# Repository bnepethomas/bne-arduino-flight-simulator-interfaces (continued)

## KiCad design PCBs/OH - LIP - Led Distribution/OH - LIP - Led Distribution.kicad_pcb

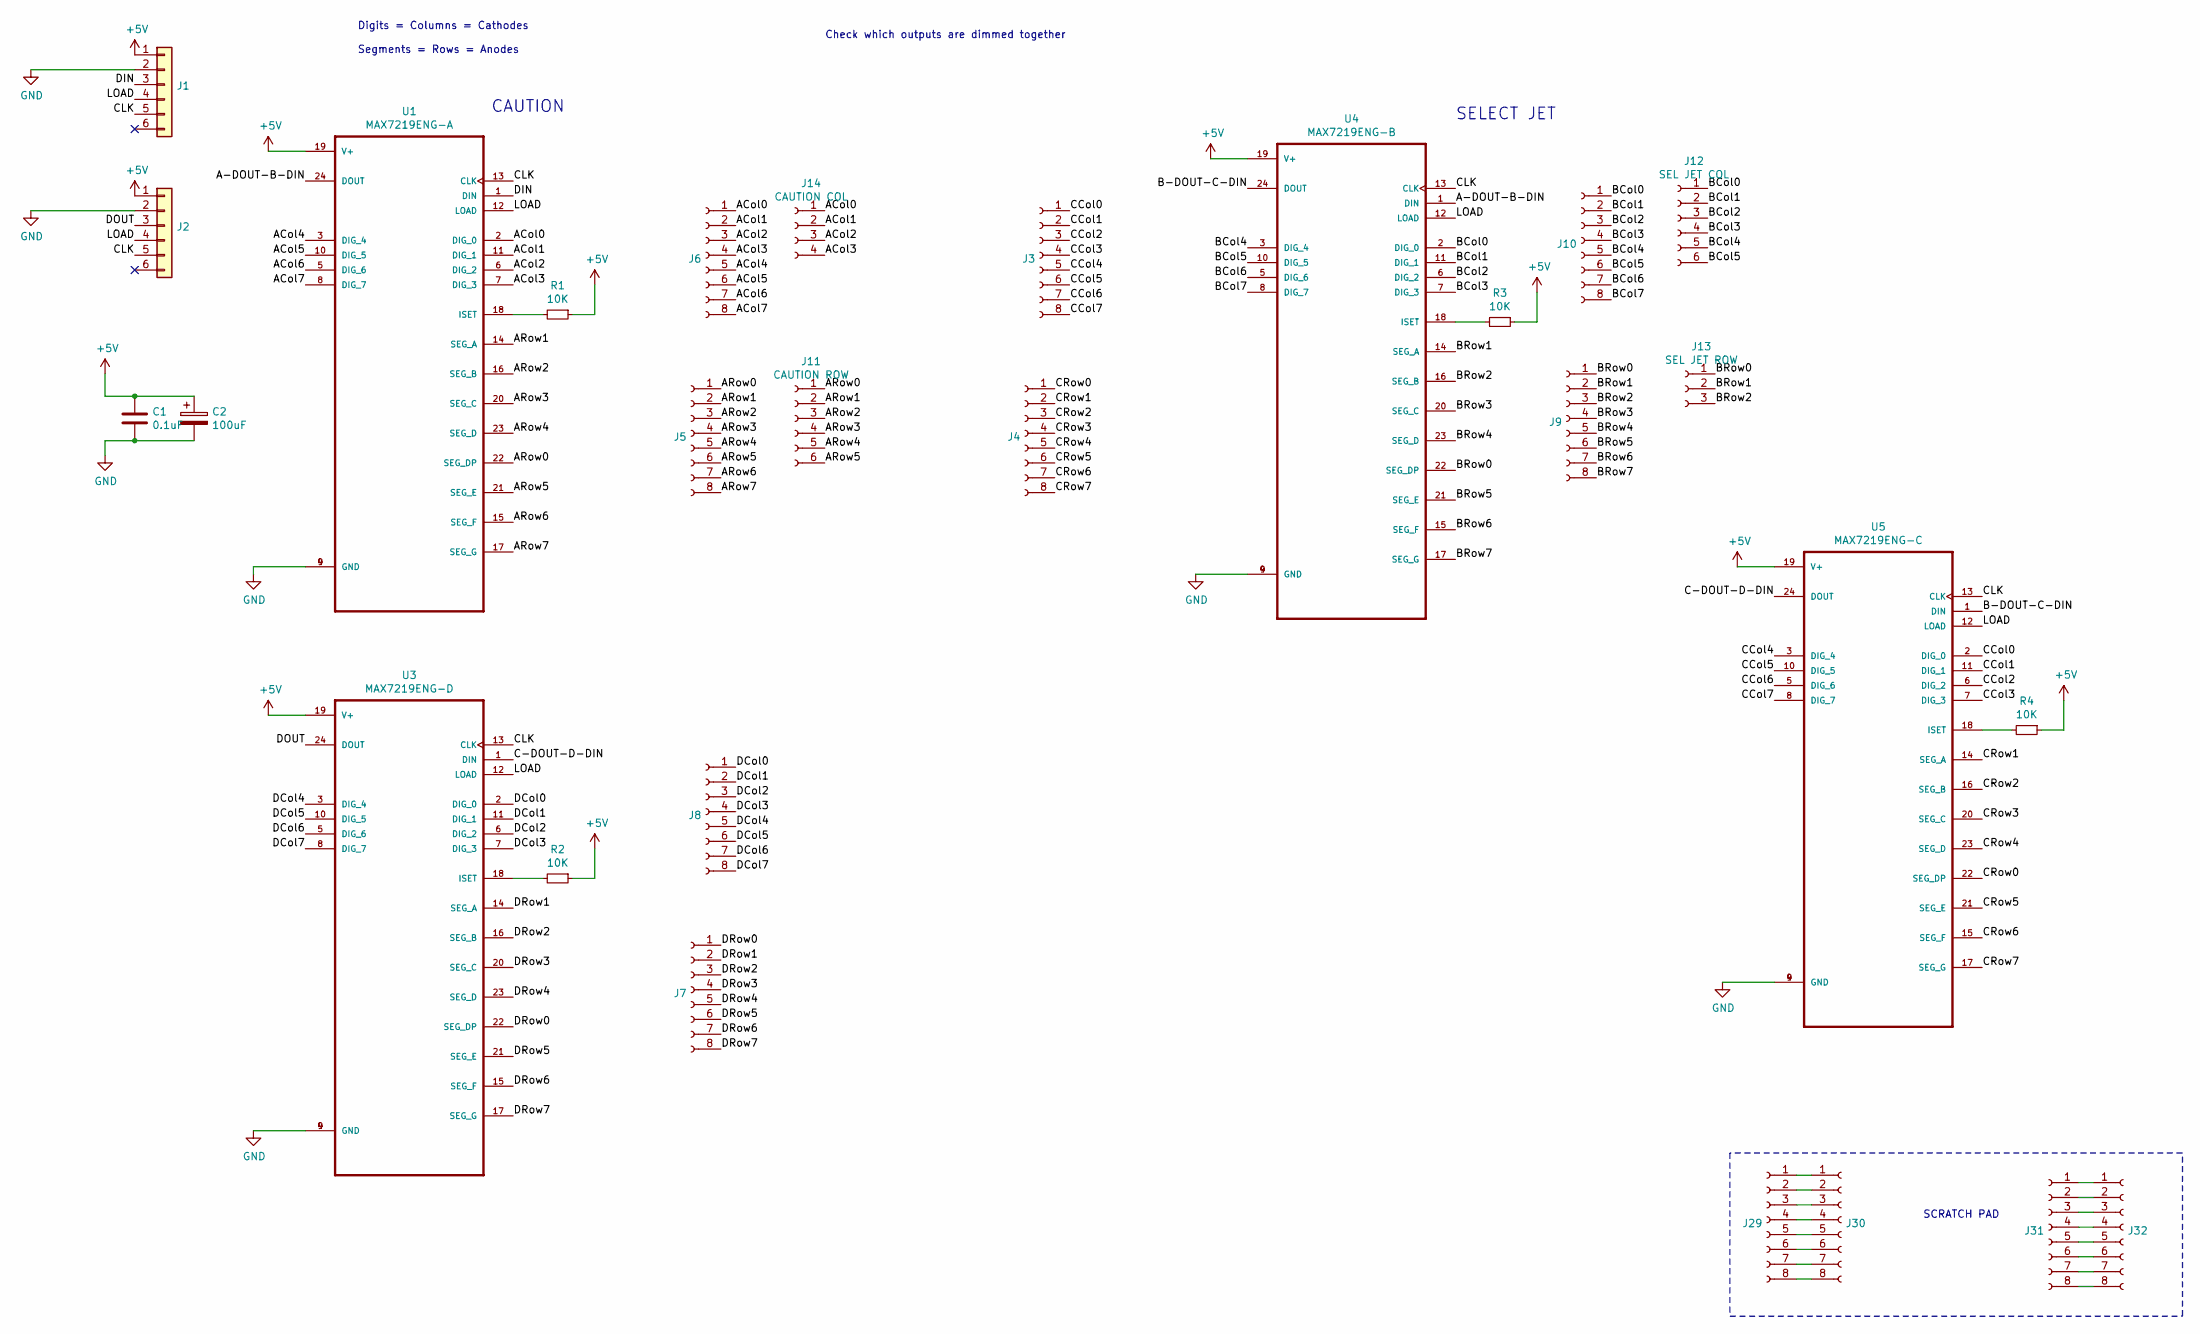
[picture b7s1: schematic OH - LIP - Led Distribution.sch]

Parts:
C1: 0.1uF; C_Disc_D5.1mm_W3.2mm_P5.00mm
C2: 100uF; CP_Radial_D8.0mm_P5.00mm
J1, J2: PinHeader_1x06_P2.54mm_Vertical
J3, J4, J5, J6, J7, J8, J9, J10, J29, J30, J31, J32: PinHeader_1x08_P2.54mm_Vertical
J11: CAUTION ROW; Molex_1x08_P2.54mm_Vertical
J12: SEL JET COL; Molex_1x06_P2.54mm_Vertical
J13: SEL JET ROW; Molex_1x03_P2.54mm_Vertical
J14: CAUTION COL; Molex_1x04_P2.54mm_Vertical
R1, R2, R3, R4: 10K; R_Axial_DIN0309_L9.0mm_D3.2mm_P5.08mm_Vertical
U1: MAX7219ENG-A; DIP-24_W7.62mm_Socket
U3: MAX7219ENG-D; DIP-24_W7.62mm_Socket
U4: MAX7219ENG-B; DIP-24_W7.62mm_Socket
U5: MAX7219ENG-C; DIP-24_W7.62mm_Socket

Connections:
+5V: C1.1, C2.1, J1.1, J2.1, R1.1, R2.1, R3.1, R4.1, U1.19 (V+), U3.19 (V+), U4.19 (V+), U5.19 (V+)
/A-DOUT-B-DIN: U1.24 (DOUT), U4.1 (DIN)
/ACol0: J6.1, J14.1, U1.2 (DIG_0)
/ACol1: J6.2, J14.2, U1.11 (DIG_1)
/ACol2: J6.3, J14.3, U1.6 (DIG_2)
/ACol3: J6.4, J14.4, U1.7 (DIG_3)
/ACol4: J6.5, U1.3 (DIG_4)
/ACol5: J6.6, U1.10 (DIG_5)
/ACol6: J6.7, U1.5 (DIG_6)
/ACol7: J6.8, U1.8 (DIG_7)
/ARow0: J5.1, J11.1, U1.22 (SEG_DP)
/ARow1: J5.2, J11.2, U1.14 (SEG_A)
/ARow2: J5.3, J11.3, U1.16 (SEG_B)
/ARow3: J5.4, J11.4, U1.20 (SEG_C)
/ARow4: J5.5, J11.5, U1.23 (SEG_D)
/ARow5: J5.6, J11.6, U1.21 (SEG_E)
/ARow6: J5.7, U1.15 (SEG_F)
/ARow7: J5.8, U1.17 (SEG_G)
/B-DOUT-C-DIN: U4.24 (DOUT), U5.1 (DIN)
/BCol0: J10.1, J12.1, U4.2 (DIG_0)
/BCol1: J10.2, J12.2, U4.11 (DIG_1)
/BCol2: J10.3, J12.3, U4.6 (DIG_2)
/BCol3: J10.4, J12.4, U4.7 (DIG_3)
/BCol4: J10.5, J12.5, U4.3 (DIG_4)
/BCol5: J10.6, J12.6, U4.10 (DIG_5)
/BCol6: J10.7, U4.5 (DIG_6)
/BCol7: J10.8, U4.8 (DIG_7)
/BRow0: J9.1, J13.1, U4.22 (SEG_DP)
/BRow1: J9.2, J13.2, U4.14 (SEG_A)
/BRow2: J9.3, J13.3, U4.16 (SEG_B)
/BRow3: J9.4, U4.20 (SEG_C)
/BRow4: J9.5, U4.23 (SEG_D)
/BRow5: J9.6, U4.21 (SEG_E)
/BRow6: J9.7, U4.15 (SEG_F)
/BRow7: J9.8, U4.17 (SEG_G)
/C-DOUT-D-DIN: U3.1 (DIN), U5.24 (DOUT)
/CCol0: J3.1, U5.2 (DIG_0)
/CCol1: J3.2, U5.11 (DIG_1)
/CCol2: J3.3, U5.6 (DIG_2)
/CCol3: J3.4, U5.7 (DIG_3)
/CCol4: J3.5, U5.3 (DIG_4)
/CCol5: J3.6, U5.10 (DIG_5)
/CCol6: J3.7, U5.5 (DIG_6)
/CCol7: J3.8, U5.8 (DIG_7)
/CLK: J1.5, J2.5, U1.13 (CLK), U3.13 (CLK), U4.13 (CLK), U5.13 (CLK)
/CRow0: J4.1, U5.22 (SEG_DP)
/CRow1: J4.2, U5.14 (SEG_A)
/CRow2: J4.3, U5.16 (SEG_B)
/CRow3: J4.4, U5.20 (SEG_C)
/CRow4: J4.5, U5.23 (SEG_D)
/CRow5: J4.6, U5.21 (SEG_E)
/CRow6: J4.7, U5.15 (SEG_F)
/CRow7: J4.8, U5.17 (SEG_G)
/DCol0: J8.1, U3.2 (DIG_0)
/DCol1: J8.2, U3.11 (DIG_1)
/DCol2: J8.3, U3.6 (DIG_2)
/DCol3: J8.4, U3.7 (DIG_3)
/DCol4: J8.5, U3.3 (DIG_4)
/DCol5: J8.6, U3.10 (DIG_5)
/DCol6: J8.7, U3.5 (DIG_6)
/DCol7: J8.8, U3.8 (DIG_7)
/DIN: J1.3, U1.1 (DIN)
/DOUT: J2.3, U3.24 (DOUT)
/DRow0: J7.1, U3.22 (SEG_DP)
/DRow1: J7.2, U3.14 (SEG_A)
/DRow2: J7.3, U3.16 (SEG_B)
/DRow3: J7.4, U3.20 (SEG_C)
/DRow4: J7.5, U3.23 (SEG_D)
/DRow5: J7.6, U3.21 (SEG_E)
/DRow6: J7.7, U3.15 (SEG_F)
/DRow7: J7.8, U3.17 (SEG_G)
/LOAD: J1.4, J2.4, U1.12 (LOAD), U3.12 (LOAD), U4.12 (LOAD), U5.12 (LOAD)
GND: C1.2, C2.2, J1.2, J2.2, U1.4 (GND), U1.9 (GND), U3.4 (GND), U3.9 (GND), U4.4 (GND), U4.9 (GND), U5.4 (GND), U5.9 (GND)
unnamed: J29.1, J30.1
unnamed: J29.2, J30.2
unnamed: J29.3, J30.3
unnamed: J29.4, J30.4
unnamed: J29.5, J30.5
unnamed: J29.6, J30.6
unnamed: J29.7, J30.7
unnamed: J29.8, J30.8
unnamed: J31.1, J32.1
unnamed: J31.2, J32.2
unnamed: J31.3, J32.3
unnamed: J31.4, J32.4
unnamed: J31.5, J32.5
unnamed: J31.6, J32.6
unnamed: J31.7, J32.7
unnamed: J31.8, J32.8
unnamed: R1.2, U1.18 (ISET)
unnamed: R2.2, U3.18 (ISET)
unnamed: R3.2, U4.18 (ISET)
unnamed: R4.2, U5.18 (ISET)

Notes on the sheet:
Digits = Columns = Cathodes Segments = Rows = Anodes
SCRATCH PAD
Check which outputs are dimmed together
CAUTION
SELECT JET

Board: 2 copper layers, 28 parts (0 on the bottom side), 93 nets, no tracks yet.

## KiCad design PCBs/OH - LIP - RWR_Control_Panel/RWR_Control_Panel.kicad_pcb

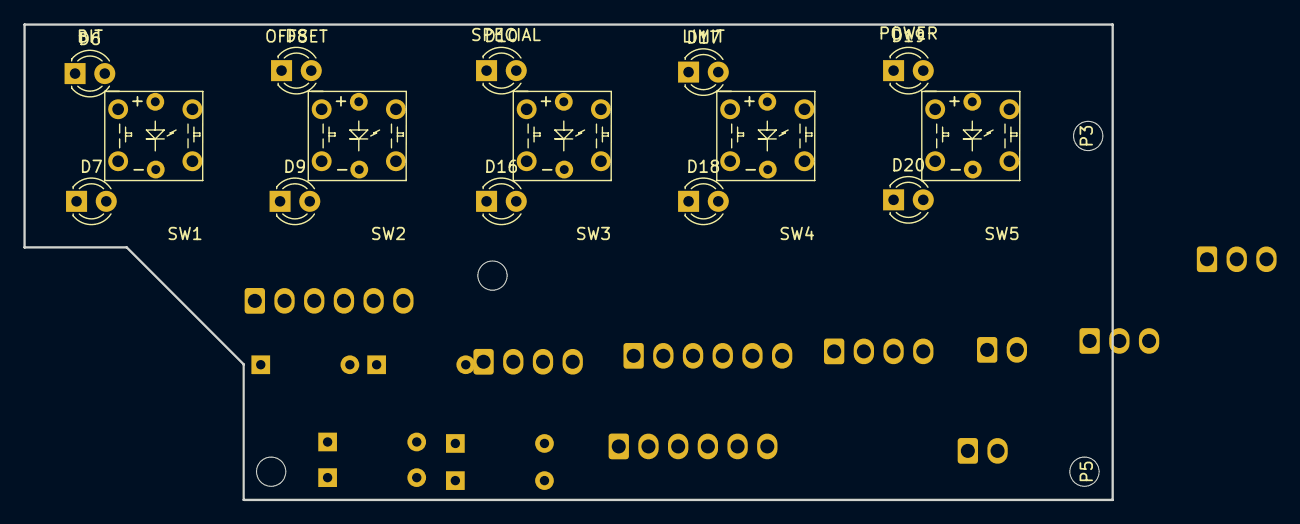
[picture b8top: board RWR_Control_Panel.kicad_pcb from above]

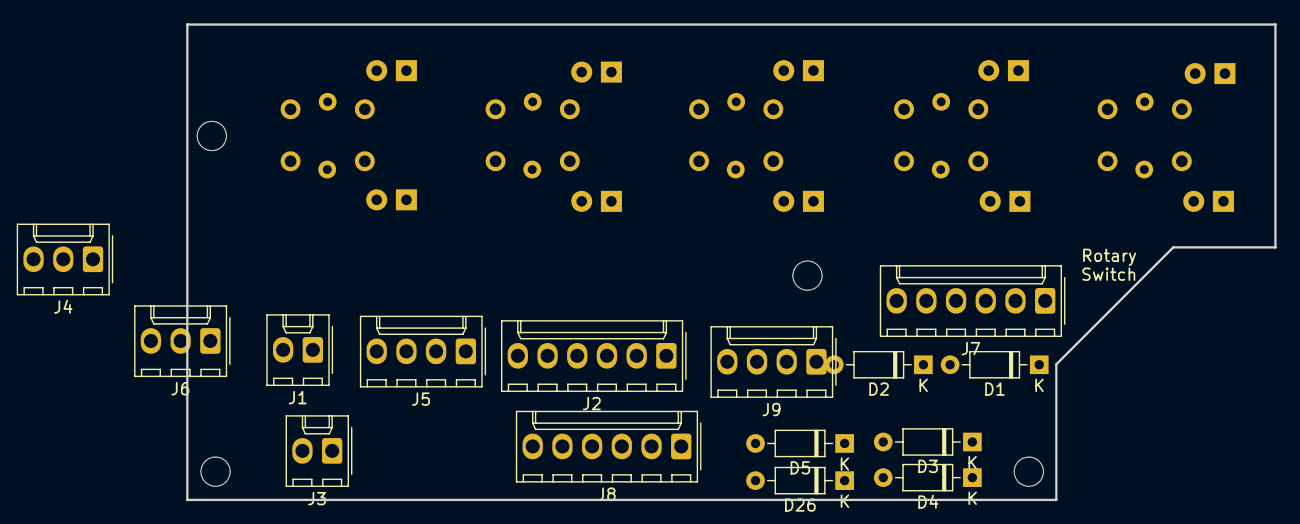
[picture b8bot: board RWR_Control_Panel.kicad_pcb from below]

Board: 2 copper layers, 93.0 x 40.6 mm, 34 parts (15 on the bottom side), 24 nets, no tracks yet.

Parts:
D1, D2, D3, D4, D5, D26: D; D_Signal_P7.62mm_Horizontal
D6, D7, D8, D9, D10, D16, D17, D18, D19, D20: LED; LED_D3.0mm
J1, J3: Conn_01x02; Molex_1x02_P2.54mm_Vertical
J2, J7, J8: PT_Conn_01x06; Molex_1x06_P2.54mm_Vertical
J4, J6: Conn_01x03; Molex_1x03_P2.54mm_Vertical
J5, J9: Conn_01x04; Molex_1x04_P2.54mm_Vertical
P3, P4, P5, P6: CONN_01X01; MountingHole_2.5mm
SW1, SW2, SW3, SW4, SW5: PT_Tactile_Switch_Led; PT_Small_Tactile_Switch_With_LED

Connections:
/Analog5V: J4.1, J5.1, J6.1
/AnalogAudio: J4.2, J5.3
/AnalogDimmer: J5.4, J6.2
/AnalogGND: J4.3, J5.2, J6.3
/Col1: D1.2, D2.2, D3.2, D4.2, D5.2, J1.1
/Col2: D26.2, J1.2
/LedCol1: D6.2, D7.2, D8.2, D9.2, D10.2, J9.1
/LedCol3: D16.2, D17.2, D18.2, D19.2, D20.2, J9.3
/LedRow1: D6.1, D16.1, J8.1
/LedRow2: D7.1, D17.1, J8.2
/LedRow3: D8.1, D18.1, J8.3
/LedRow4: D9.1, D19.1, J8.4
/LedRow5: D10.1, D20.1, J8.5
/Row1: J2.1, J7.2, SW1.3, SW1.4
/Row2: J2.2, J7.3, SW2.3, SW2.4
/Row3: J2.3, J7.4, SW3.3, SW3.4
/Row4: J2.4, J7.5, SW4.3, SW4.4
/Row5: J2.5, J7.6, SW5.3, SW5.4
unnamed: D1.1, SW1.1, SW1.2
unnamed: D2.1, SW2.1, SW2.2
unnamed: D3.1, SW3.1, SW3.2
unnamed: D4.1, SW4.1, SW4.2
unnamed: D5.1, SW5.1, SW5.2
unnamed: D26.1, J7.1
